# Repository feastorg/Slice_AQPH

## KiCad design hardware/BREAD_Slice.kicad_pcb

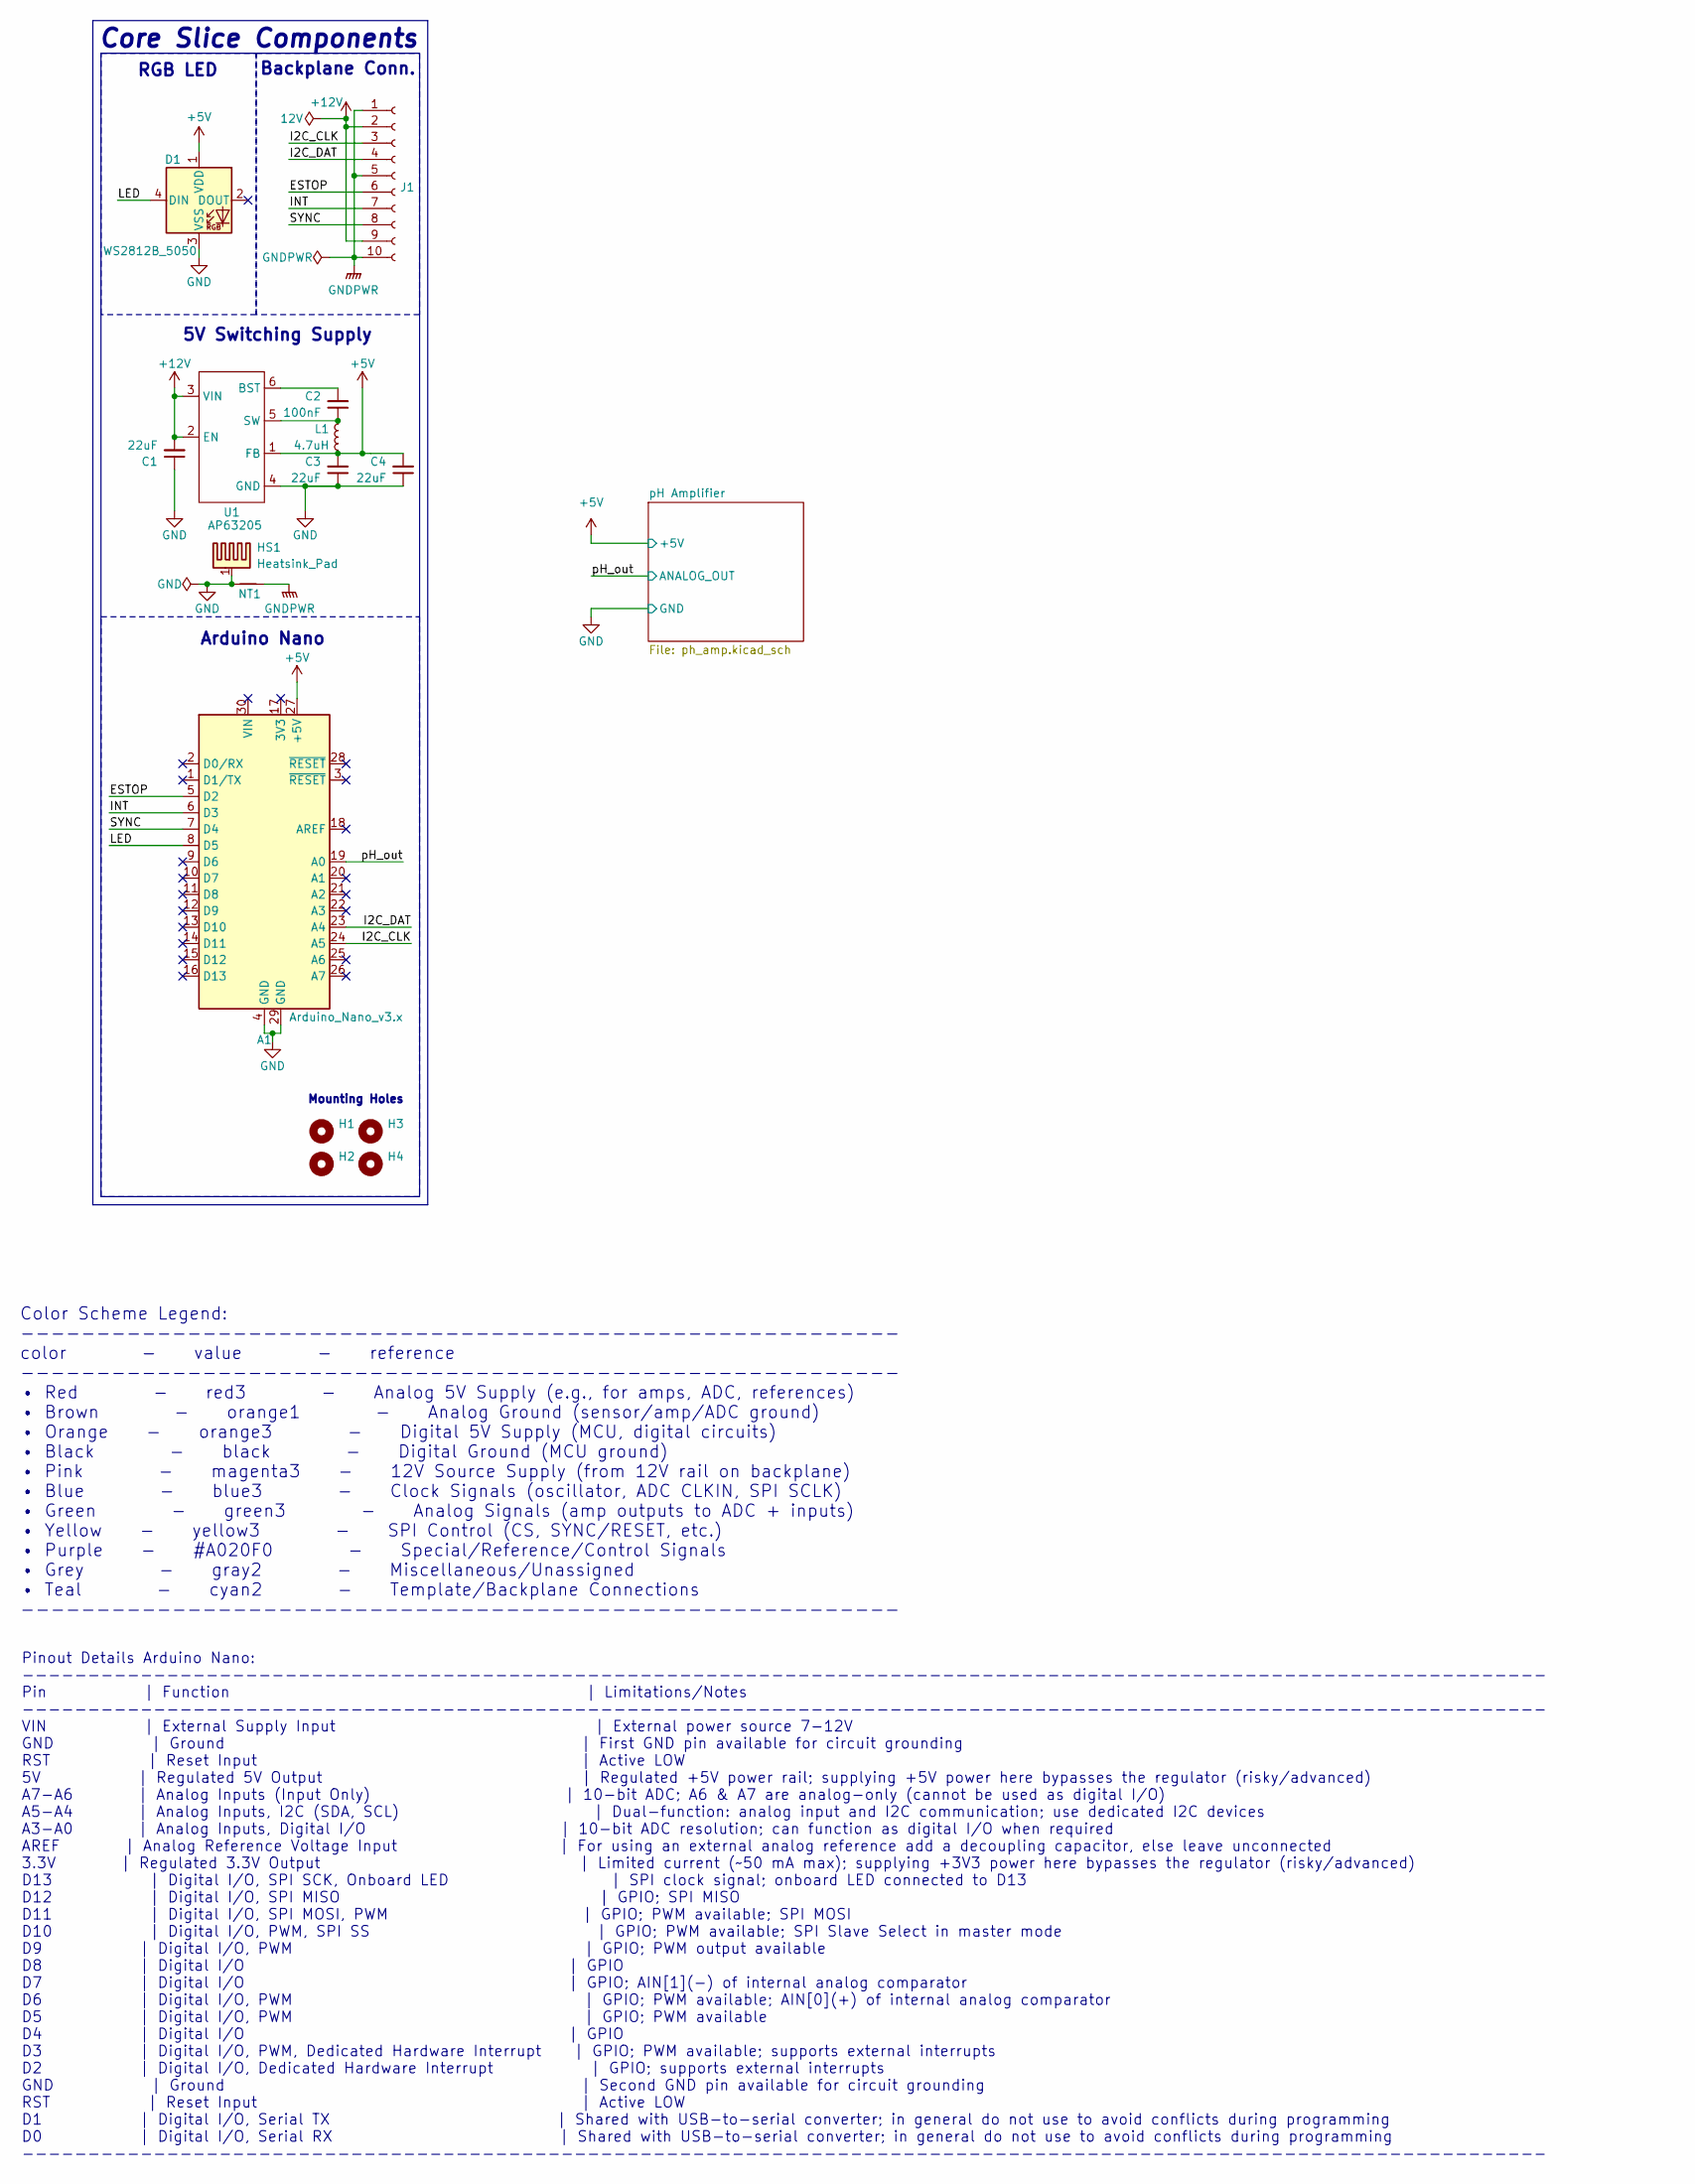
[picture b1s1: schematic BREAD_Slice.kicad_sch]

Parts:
A1: Arduino_Nano_v3.x; Arduino_Nano
C1, C3, C4: 22uF; C_1206_3216Metric
C2: 100nF; C_1206_3216Metric
D1: WS2812B_5050; WS2812-5050-4PIN
H1, H2, H3, H4: MountingHole; MountingHole_5mm
HS1: Heatsink_Pad; Thermal_Pad
J1: Conn_01x10_Female; PinSocket_1x10_P2.54mm_Horizontal
L1: 4.7uH; L_1210_3225Metric
NT1: NetTie_2; NetTie-2_SMD_Pad2.0mm
U1: AP63205; TSOT-23-6

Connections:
+5V: A1.27 (+5V), C3.2, C4.2, D1.1 (VDD), L1.2, U1.1 (FB); also elsewhere on the board
+12V: C1.2, J1.2, J1.9, U1.2 (EN), U1.3 (VIN)
/ESTOP: A1.5 (D2), J1.6
/I2C_CLK: A1.24 (A5), J1.3
/I2C_DAT: A1.23 (A4), J1.4
/INT: A1.6 (D3), J1.7
/LED: A1.8 (D5), D1.4 (DIN)
/SYNC: A1.7 (D4), J1.8
/pH_out: A1.19 (A0); also elsewhere on the board
GND: A1.4 (GND), A1.29 (GND), C1.1, C3.1, C4.1, D1.3 (VSS), HS1.1, NT1.1, U1.4 (GND); also elsewhere on the board
GNDPWR: J1.1, J1.5, J1.10, NT1.2
unnamed: C2.2, U1.6 (BST)
unnamed: C2.1, L1.1, U1.5 (SW)

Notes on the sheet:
5V Switching Supply
Pinout Details Arduino Nano: -------------------------------------------------------------------------------------------------------------------- Pin | Function | Limitations/Notes -------------------------------------------------------------------------------------------------------------------- V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
RGB LED
Color Scheme Legend: ---------------------------------------------------------- color - value - reference ---------------------------------------------------------- • Red - red3 - Analog 5V Supply (e.g., for amps, ADC, references) • Brown - orange1 - Analog Ground (sensor/amp/ADC ground) • Orange -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
Core Slice Components
Arduino Nano
Mounting Holes
Backplane Conn.

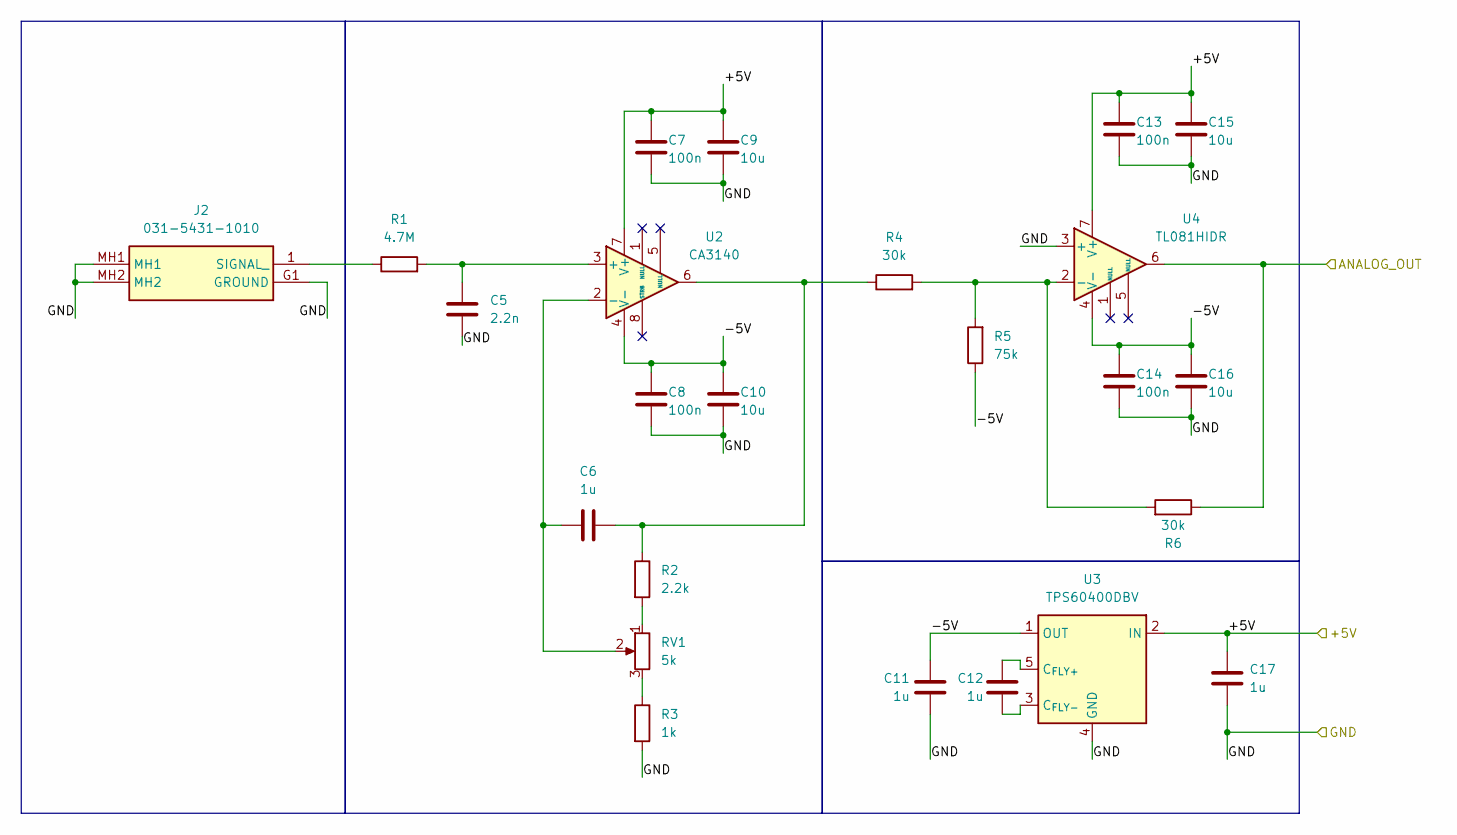
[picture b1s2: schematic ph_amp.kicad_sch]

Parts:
C5: 2.2n; C_0805_2012Metric_Pad1.18x1.45mm_HandSolder
C6, C11, C12, C17: 1u; C_0805_2012Metric_Pad1.18x1.45mm_HandSolder
C7, C8, C13, C14: 100n; C_0805_2012Metric_Pad1.18x1.45mm_HandSolder
C9, C10, C15, C16: 10u; C_1206_3216Metric_Pad1.33x1.80mm_HandSolder
J2: 031-5431-1010; 03154311010; Mouser Part Number 523-31-5431-1010
R1: 4.7M; R_0805_2012Metric_Pad1.20x1.40mm_HandSolder
R2: 2.2k; R_0805_2012Metric_Pad1.20x1.40mm_HandSolder
R3: 1k; R_0805_2012Metric_Pad1.20x1.40mm_HandSolder
R4, R6: 30k; R_0805_2012Metric_Pad1.20x1.40mm_HandSolder
R5: 75k; R_0805_2012Metric_Pad1.20x1.40mm_HandSolder
RV1: 5k; Potentiometer_Bourns_3296W_Vertical
U2: CA3140; SOIC-8_3.9x4.9mm_P1.27mm
U3: TPS60400DBV; SOT-23-5
U4: TL081HIDR; SOIC-8_3.9x4.9mm_P1.27mm

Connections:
+5V: C7.1, C9.1, C13.1, C15.1, C17.1, U2.7 (V+), U3.2 (IN), U4.7 (V+); also elsewhere on the board
/pH Amplifier/-5V: C8.1, C10.1, C11.1, C14.1, C16.1, R5.1, U2.4 (V-), U3.1 (OUT), U4.4 (V-)
/pH_out: R6.1, U4.6; also elsewhere on the board
GND: C5.2, C7.2, C8.2, C9.2, C10.2, C11.2, C13.2, C14.2, C15.2, C16.2, C17.2, J2.G1 (GROUND), J2.MH1, J2.MH2, R3.2, U3.4 (GND), U4.3 (+); also elsewhere on the board
unnamed: C6.2, R2.1, R4.1, U2.6
unnamed: J2.1 (SIGNAL_), R1.1
unnamed: R2.2, RV1.1
unnamed: R3.1, RV1.3
unnamed: C5.1, R1.2, U2.3 (+)
unnamed: C6.1, RV1.2, U2.2 (-)
unnamed: C12.1, U3.5 (C_{FLY+})
unnamed: C12.2, U3.3 (C_{FLY-})
unnamed: R4.2, R5.2, R6.2, U4.2 (-)

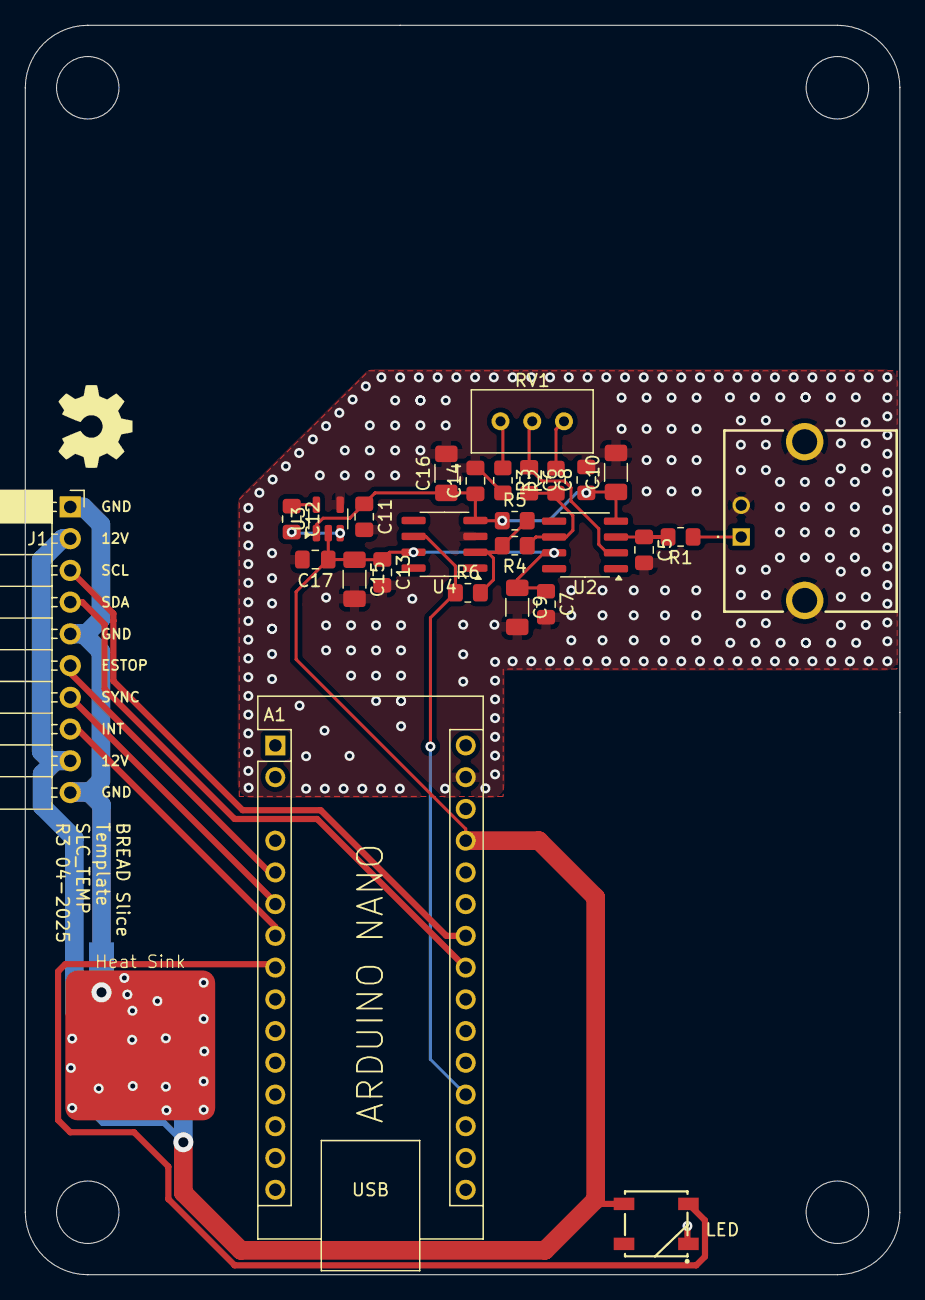
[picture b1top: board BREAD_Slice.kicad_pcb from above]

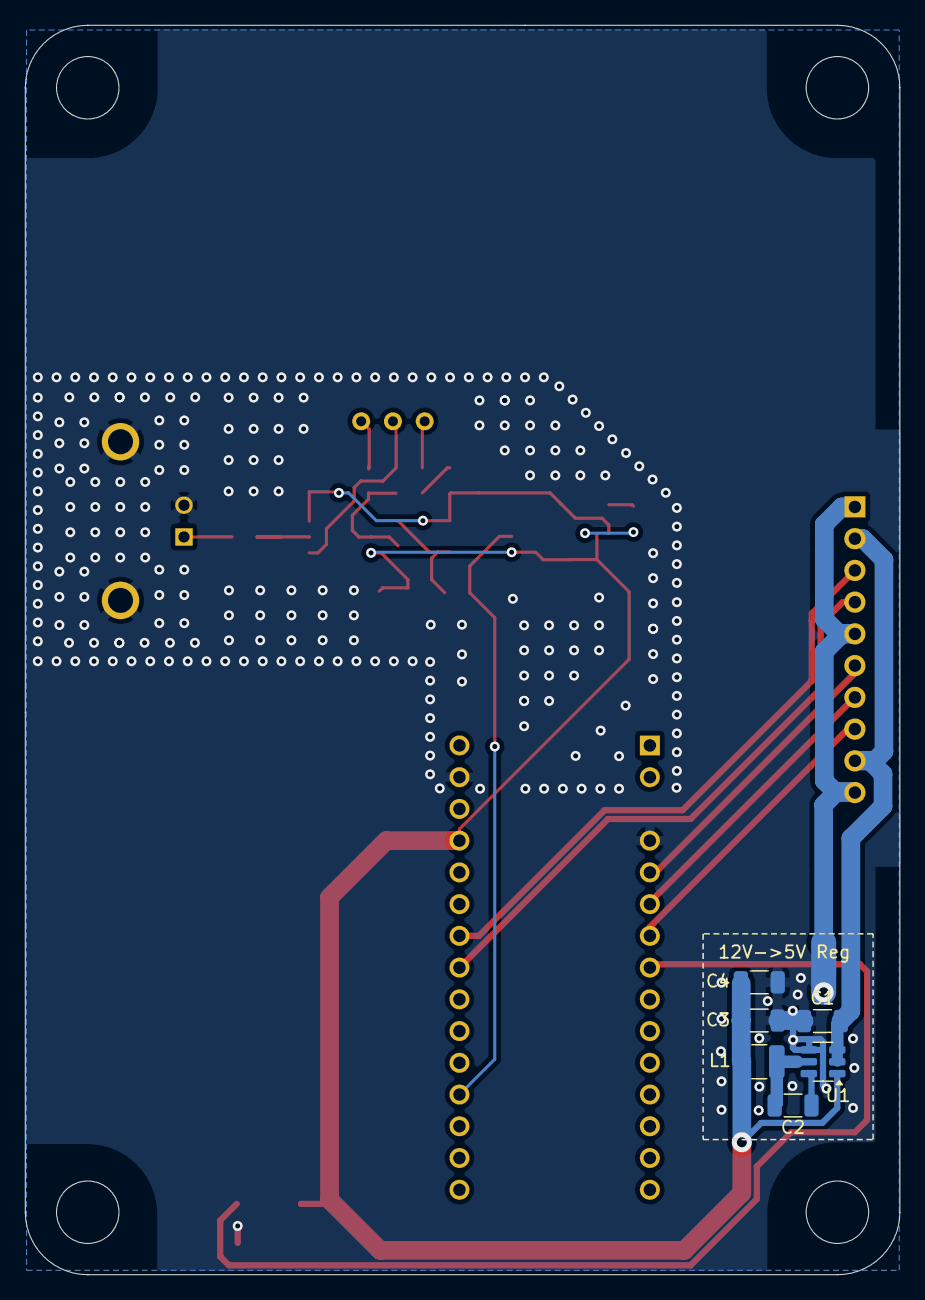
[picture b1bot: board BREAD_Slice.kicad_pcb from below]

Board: 2 copper layers, 70.0 x 100.0 mm, 40 parts (7 on the bottom side), 23 nets.

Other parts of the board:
Logo1: Logo_Open_Hardware_Small; OSHW-Symbol_6.7x6mm_SilkScreen

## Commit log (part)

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2025-04-17 updated docs
2025-04-17 added reference
2026-04-18 chore: minor update
2026-05-20 Add slice.yaml manifest (schema v1.0)
2026-05-24 Add KiBot/docs pipeline
2026-05-24 Update TODO with CI findings (DRC errors)
